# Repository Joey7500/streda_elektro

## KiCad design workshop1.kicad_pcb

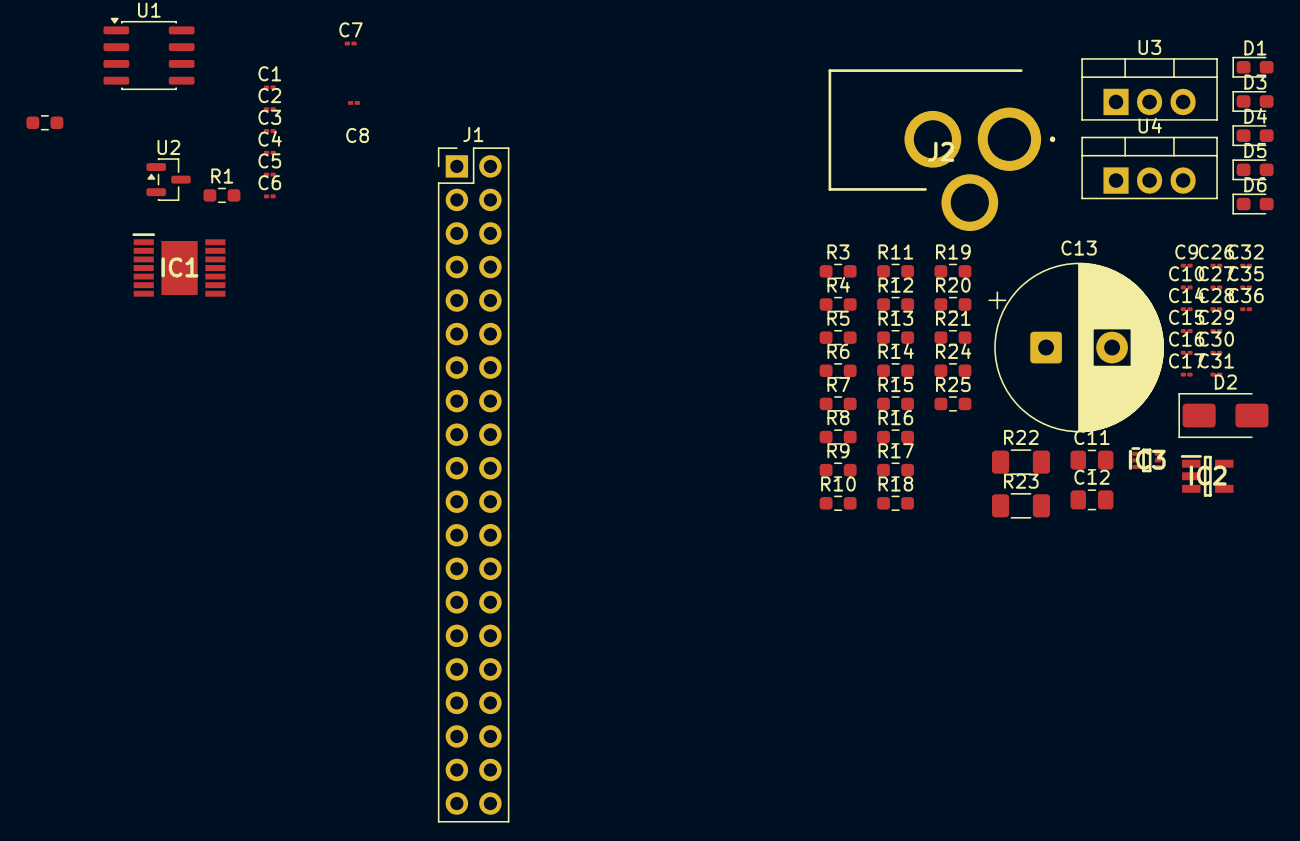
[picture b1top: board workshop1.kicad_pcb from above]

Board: 2 copper layers, 66 parts (0 on the bottom side), 39 nets, no tracks yet.

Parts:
C1, C3, C5, C7, C15, C16, C28: 100n; C_01005_0402Metric
C2, C4, C6, C8, C17: 1u; C_01005_0402Metric
C9, C31: 100n/50V; C_01005_0402Metric
C10, C32: 1u/50V; C_01005_0402Metric
C11, C12: 4u7/50V; C_0805_2012Metric_Pad1.18x1.45mm_HandSolder
C13: UPW1E102MHD; CP_Radial_D12.5mm_P5.00mm
C14: C_01005_0402Metric
C26, C27, C35, C36: 4n7; C_01005_0402Metric
C29, C30: 2n2; C_01005_0402Metric
D1, D3, D4, D5, D6: LED; LED_0603_1608Metric_Pad1.05x0.95mm_HandSolder
D2: B340A-E3/61T; D_SMA
IC1: TLE94004EP; SOP65P600X115-15N
IC2: MCP1416RT-E_OT; SOT95P270X145-5N
IC3: TMP112DQDRLRQ1; SOTFL50P160X60-6N
J1: Raspberry_Pi_2_3; PinHeader_2x20_P2.54mm_Vertical
J2: 694106301002
R1: R; R_0603_1608Metric_Pad0.98x0.95mm_HandSolder
R2: 0R1; R_0603_1608Metric_Pad0.98x0.95mm_HandSolder
R3, R4, R12: 1k; R_0603_1608Metric_Pad0.98x0.95mm_HandSolder
R5, R6, R7, R8, R9, R10, R18, R19, R21: 100R; R_0603_1608Metric_Pad0.98x0.95mm_HandSolder
R11, R17: 22k; R_0603_1608Metric_Pad0.98x0.95mm_HandSolder
R13: 4k7; R_0603_1608Metric_Pad0.98x0.95mm_HandSolder
R14, R24, R25: 3k3; R_0603_1608Metric_Pad0.98x0.95mm_HandSolder
R15, R16: 47R; R_0603_1608Metric_Pad0.98x0.95mm_HandSolder
R20: 22K; R_0603_1608Metric_Pad0.98x0.95mm_HandSolder
R22, R23: 22K; R_1206_3216Metric_Pad1.30x1.75mm_HandSolder
U1: INA240A1D; SOIC-8_3.9x4.9mm_P1.27mm
U2: TPS7A0533PDBZ; SOT-23
U3, U4: LM78M05_TO220; TO-220-3_Vertical

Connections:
+3.3V: C7.1, C8.1, IC1.14 (VDD), IC3.5 (V+), J1.1 (3V3), J1.17 (3V3), R14.1, R24.1, R25.1
+3.3VA: C1.1, C2.1, C3.1, C4.1, C16.1, C17.1, U1.3 (REF2), U1.6 (V+), U2.2 (VO)
+5V: C5.1, C6.1, C31.1, C32.1, IC2.5 (VDD), J1.2 (5V), J1.4 (5V), R13.1, U2.3 (VI), U3.3 (VO), U4.3 (VO)
+12V: C11.1, C12.1, C13.1, D2.1 (K), IC1.5 (VS), R11.1, U3.1 (VI), U4.1 (VI)
DRV_ENA: J1.32 (PWM0/GPIO12), J1.33 (PWM1/GPIO13), R8.1, R9.2, R10.2
ERR_FLAG_TO_UC: IC1.13 (EF), R3.1, R4.1
GND: C1.2, C2.2, C3.2, C4.2, C5.2, C6.2, C7.2, C8.2, C9.2, C10.2, C11.2, C12.2, C13.2, C14.2, C15.2, C16.2, C17.2, C26.2, C27.2, C28.2, C29.2, C30.2, C31.2, C32.2, C35.2, C36.2, IC1.8 (GND), IC1.15 (EP), IC3.2 (GND), IC3.4 (ADD0), J1.6 (GND), J1.9 (GND), J1.14 (GND), J1.20 (GND), J1.25 (GND), J1.30 (GND), J1.34 (GND), J1.39 (GND), J2.2 (GND_1), J2.3 (GND_2), R20.2, R22.2, R23.2, U1.2 (GND), U1.4 (GND), U1.7 (REF1), U2.1 (GND), U3.2 (GND), U4.2 (GND)
unnamed: C26.1, R15.2
unnamed: C27.1, R16.2
unnamed: D1.2 (A_2), R4.2
unnamed: D2.2 (A), J2.1 (POWER)
unnamed: D3.2 (A_2), R11.2
unnamed: D4.2 (A_2), R12.2
unnamed: D5.2 (A_2), R13.2
unnamed: D6.2 (A_2), R14.2
unnamed: IC1.11 (EN1), R10.1
unnamed: IC1.12 (EN2), R9.1
unnamed: IC1.1 (IN_1), R6.2
unnamed: IC1.2 (IN_2), R7.2
unnamed: IC1.3 (IN_3), R8.2
unnamed: IC1.4 (IN_4), R5.2
unnamed: C14.1, IC1.7 (OUT_1), R15.1
unnamed: C15.1, IC1.9 (OUT_2), R16.1
unnamed: IC2.3 (IN), R20.1, R21.2
unnamed: IC2.4 (OUT), R22.1, R23.1
unnamed: C29.1, J1.36 (GPIO16), R18.2
unnamed: J1.15 (GPIO22), R3.2
unnamed: J1.18 (GPIO24), R12.1
unnamed: C30.1, J1.22 (GPIO25), R19.2
unnamed: R2.2, U1.1 (-)
unnamed: R2.1, U1.8 (+)
PWM_0: J1.13 (GPIO27), R6.1
PWM_2: J1.23 (SCLK0/GPIO11), R7.1
PWM_4: J1.37 (GPIO26), R5.1
PWM_RESISTOR: J1.16 (GPIO23), R21.1
SCL: IC3.1 (SCL), J1.5 (SCL/GPIO3), R25.2
SDA: IC3.6 (SDA), J1.3 (SDA/GPIO2), R24.2
SHUNT_FLT: C28.1, R17.2, R18.1
SHUNT_RAW: R17.1, R19.1, U1.5
